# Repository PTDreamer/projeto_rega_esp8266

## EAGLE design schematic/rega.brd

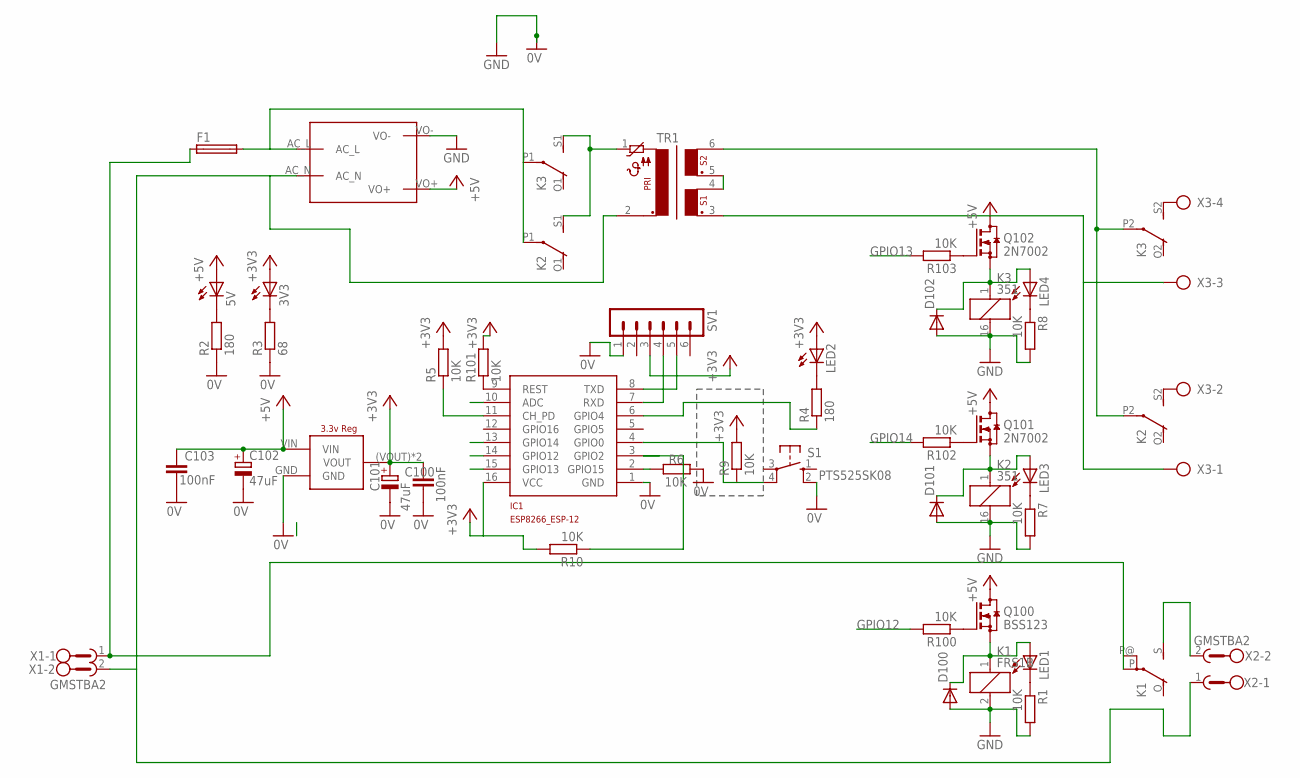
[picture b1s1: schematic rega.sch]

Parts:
3V3, 5V: LEDCHIPLED_0805; CHIPLED_0805
C100, C103: 100nF; C0805
C101, C102: 47uF; CT3528
D100, D101, D102: DIODE-SOD80C; SOD80C
F1: LITTLEFUSESMD; SMD
IC1: ESP8266_ESP-12; ESP8266-ESP12
K1: FRS1B
K2, K3: 351
LED1, LED3, LED4: LEDSML0805; SML0805
LED2: LEDCHIPLED_0805; CHIPLED_0805
Q100: BSS123; SOT23
Q101, Q102: 2N7002; SOT23
R1, R5, R6, R7, R8, R9, R10, R100, R101, R102, R103: 10K; R0805
R2, R4: 180; R0805
R3: 68; R0805
S1: PTS525SK08; SM08
SV1: MA06-1
TR1: PT13-2
U$1: MAINS_CONVERTERS; HLK-PM01
U$100: LD1117; LD1117SOT-223
X1, X2: GMSTBA2
X3: AK300/4

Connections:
+3V3: 3V3.A, C100.1, C101.+, IC1.16 (VCC), LED2.A, R5.2, R9.2, R10.2, R101.2, SV1.3, U$100.(VOUT) (VOUT), U$100.VOUT
+5V: 5V.A, C102.+, C103.1, Q100.3 (D), Q101.3 (D), Q102.3 (D), U$1.VO+, U$100.VIN
ADC: IC1.10 (ADC)
GND: C100.2, C101.-, C102.-, C103.2, D100.A, D101.A, D102.A, IC1.1 (GND), K1.2, K2.16 (2), K3.16 (2), R1.2, R2.1, R3.1, R6.2, R7.2, R8.2, S1.2 (S), SV1.1, U$1.VO-, U$100.GND
GPIO2: IC1.3 (GPIO2), R10.1
GPIO12: IC1.14 (GPIO12), R100.2
GPIO13: IC1.15 (GPIO13), R103.2
GPIO14: IC1.13 (GPIO14), R102.2
unnamed: F1.P$1 (1), K1.P, K1.P@, X1.1
unnamed: Q102.1 (G), R103.1
unnamed: IC1.2 (GPIO15), R6.1
unnamed: F1.P$2 (2), K2.P1, K3.P1, U$1.AC_L
unnamed: TR1.2, U$1.AC_N, X1.2, X2.1
unnamed: IC1.4 (GPIO0), R9.1, S1.4
unnamed: IC1.11 (CH_PD), R5.1
unnamed: D101.C, K2.1, LED3.A, Q101.2 (S)
unnamed: 5V.C, R2.2
unnamed: TR1.3, X3.1, X3.3
unnamed: LED4.C, R8.1
unnamed: 3V3.C, R3.2
unnamed: IC1.9 (REST), R101.1
unnamed: LED2.C, R4.2
unnamed: IC1.6 (GPIO4), R4.1
unnamed: D102.C, K3.1, LED4.A, Q102.2 (S)
unnamed: K2.P2, K3.P2, TR1.6
unnamed: K3.S2 (S), X3.4
unnamed: K2.S1 (S), K3.S1 (S), TR1.1
unnamed: K2.S2 (S), X3.2
unnamed: K1.S, X2.2
unnamed: TR1.4, TR1.5
unnamed: Q100.1 (G), R100.1
unnamed: Q101.1 (G), R102.1
unnamed: LED3.C, R7.1
unnamed: LED1.C, R1.1
unnamed: D100.C, K1.1, LED1.A, Q100.2 (S)
RXD: IC1.7 (RXD), SV1.4
TXD: IC1.8 (TXD), SV1.5

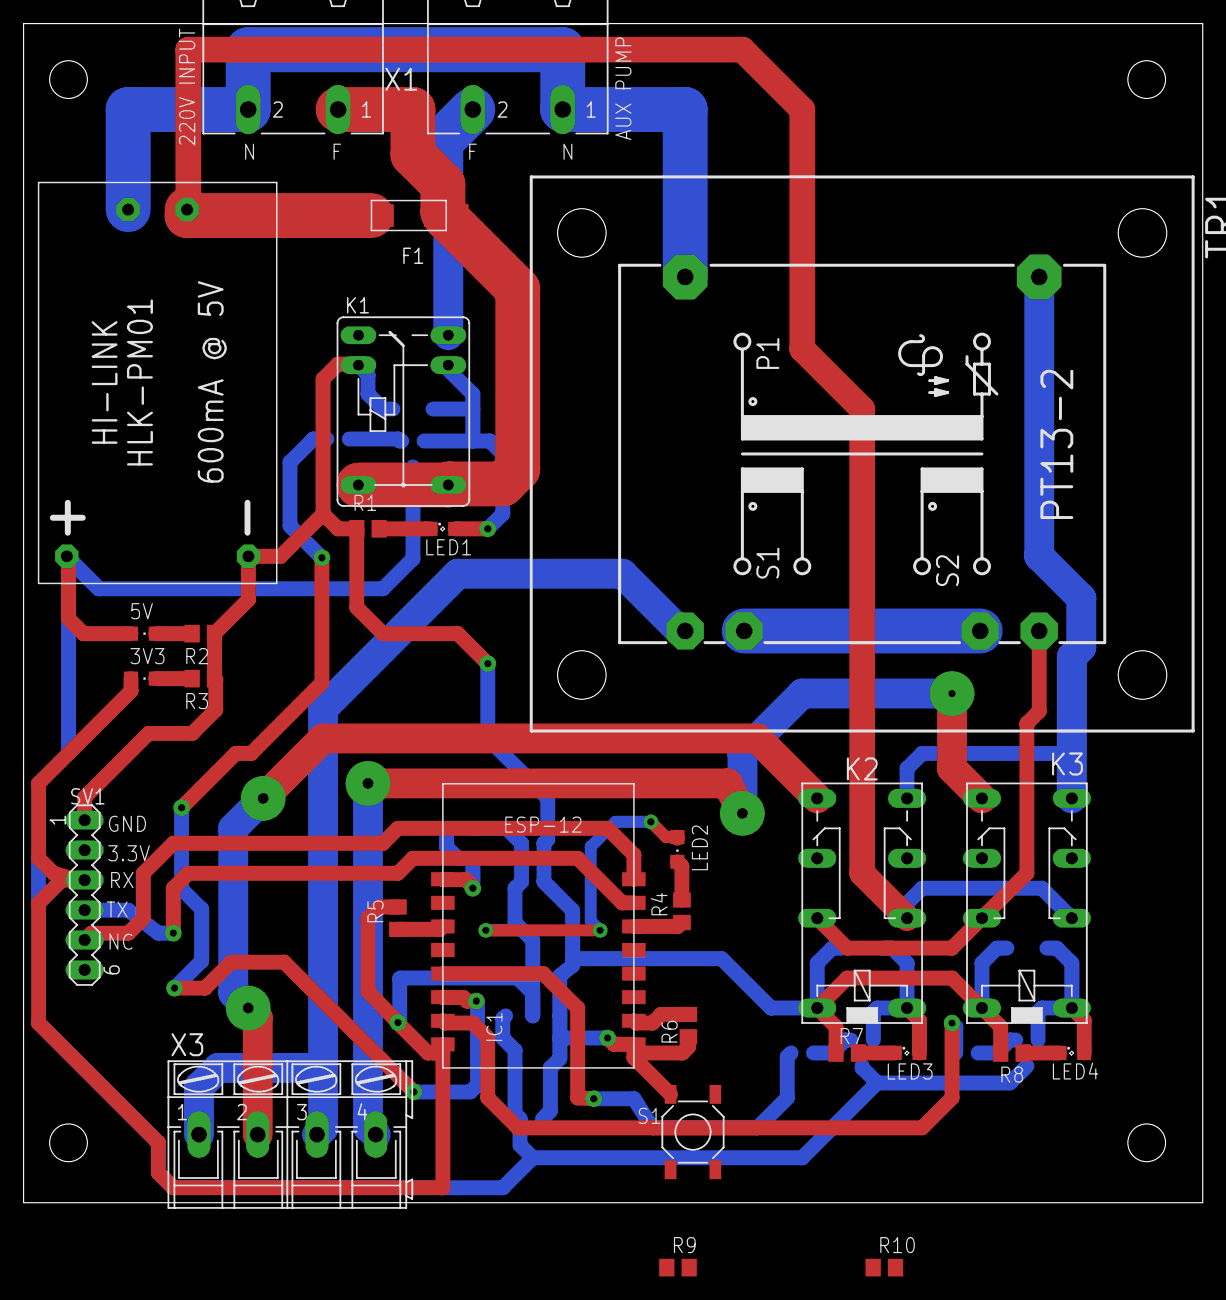
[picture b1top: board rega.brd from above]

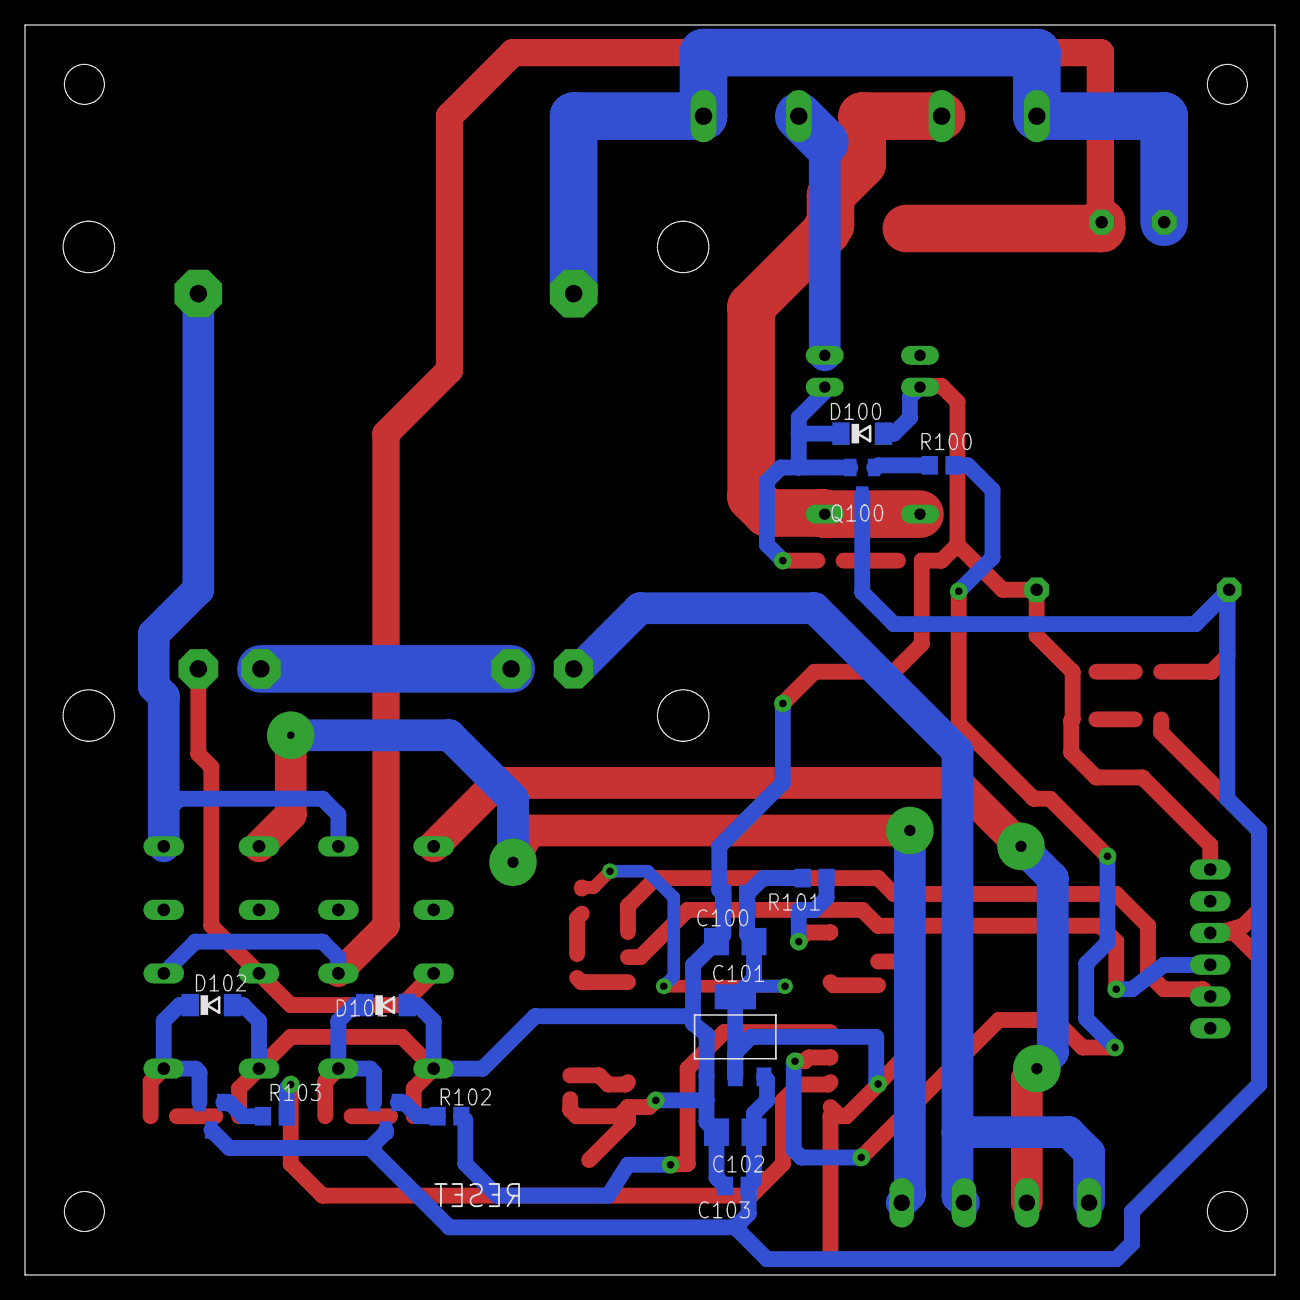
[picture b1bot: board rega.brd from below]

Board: 2 copper layers, 100.0 x 100.0 mm, 43 parts (15 on the bottom side), 36 nets.

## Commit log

2016-07-26 production version
2016-12-05 last changes
2017-06-18 Added HW files
2017-06-18 v2 changes
2017-06-18 other files
    TODO check if these are used
2017-06-19 HW add missing resistor GPIO2 High
2017-06-19 Added used libs
2017-07-26 new hardware changes
2020-07-26 Fix chunked receive
2021-06-08 SPIFFS issue
    Filename size
2023-08-05 Updated for larger schedules
